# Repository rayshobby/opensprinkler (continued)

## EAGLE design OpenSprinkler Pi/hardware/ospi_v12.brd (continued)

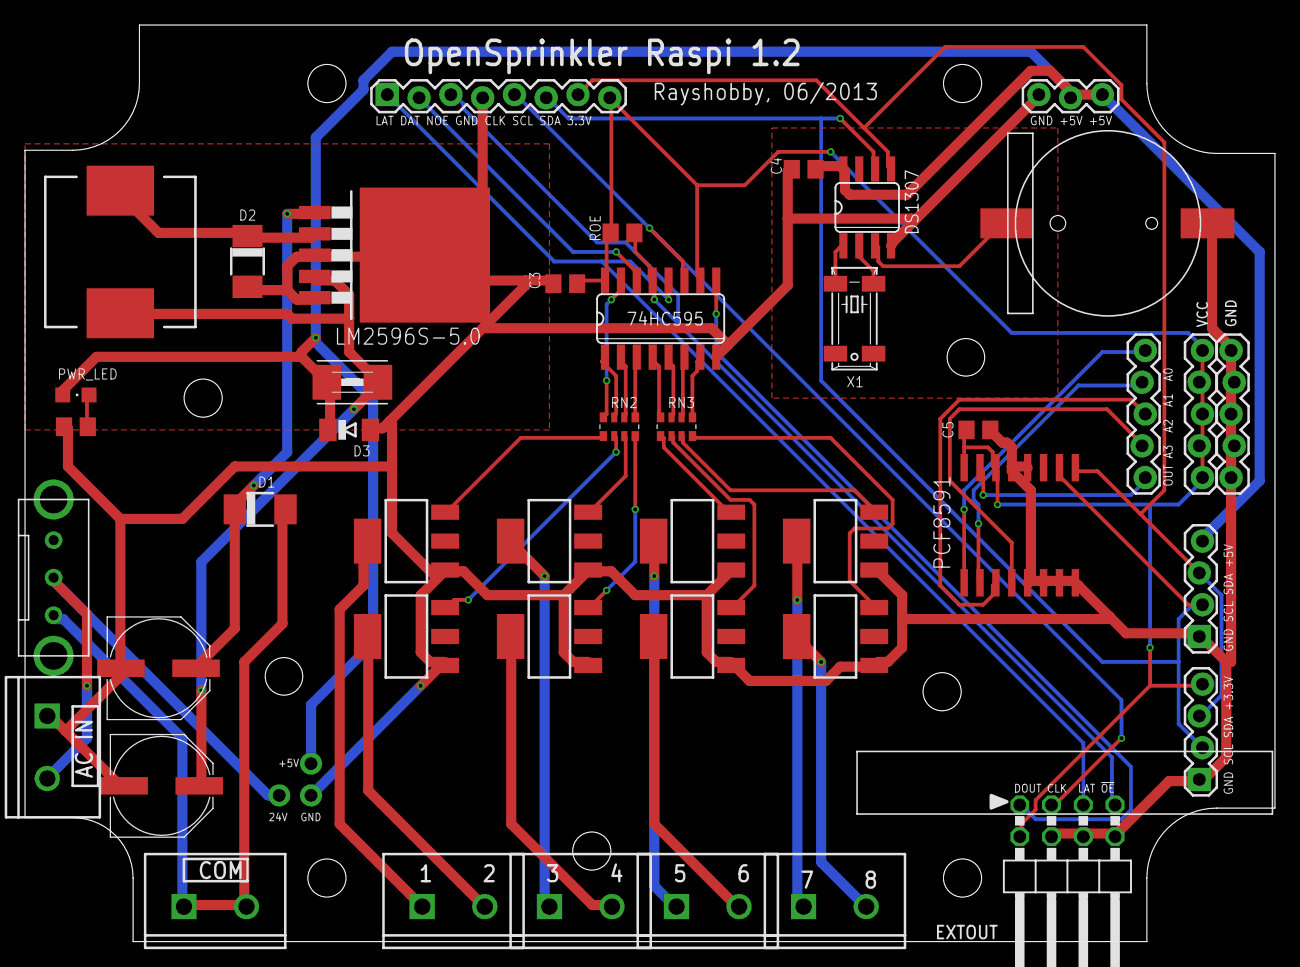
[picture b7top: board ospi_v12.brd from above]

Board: 2 copper layers, 99.9 x 73.3 mm, 48 parts (0 on the bottom side), 48 nets.

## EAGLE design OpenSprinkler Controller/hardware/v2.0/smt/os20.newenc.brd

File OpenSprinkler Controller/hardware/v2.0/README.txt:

OpenSprinkler v2.0 (2nd generation)
Changes from 1st generation:

- Microcontroller upgraded to ATmega644
- Switching regulator upgraded to LM2596S-5.0 (from MC34063)
- Added microSD card slot
- Added support for LCD backlight and contrast adjustments
- Added pull-up resistor (RPR) for automatic detection of extension boards.
- More digital and analog I/O pins, and extra pin headers for connecting RF transmitter.

Schematics and Board design files require EagleCAD v6.0 or above.

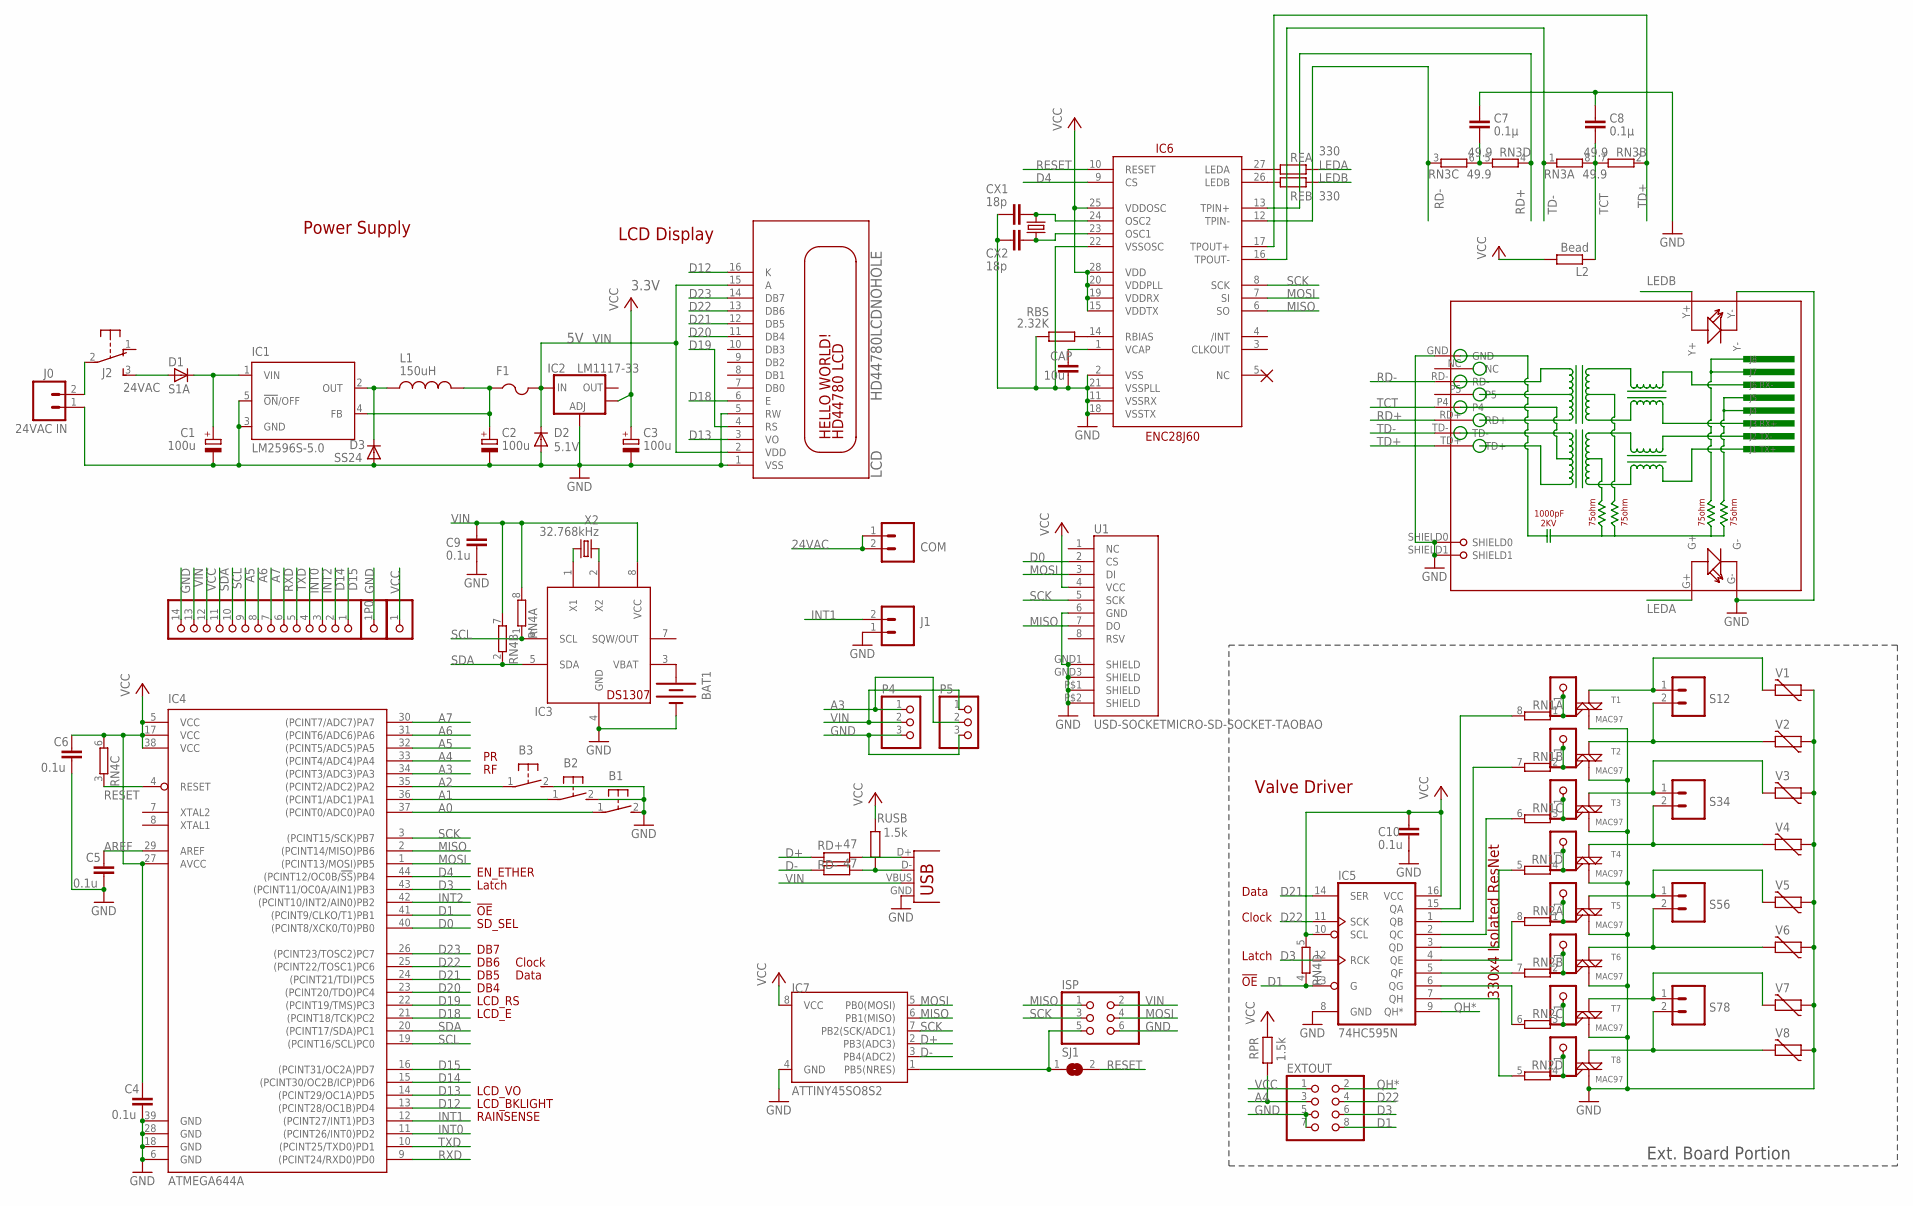
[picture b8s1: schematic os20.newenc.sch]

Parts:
B1, B2, B3: 31-XX; B3F-31XX
BAT1: BATTERYBATTERY_12MM_SMT; BATTCON_12MM_SMT
C1: 100u; E3,5-8
C2, C3: 100u; PANASONIC_D
C4, C5, C6, C9, C10: 0.1u; C0805
C7, C8: 0.1µ; C0805
CAP: 10u; C0805
COM: M025MM; SCREWTERMINAL-5MM-2
CX1, CX2: 18p; C0805
D1: S1A; DO-214AC
D2: 5.1V; MINIMELF
D3: SS24; DO-214AC
EXTOUT: PINHD-2X4; 2X04
F1: PTCFUSE-1812; 1812
IC1: LM2596S-5.0; TO263-5
IC2: LM1117-33; SOT223
IC3: DS1307; SO08
IC4: ATMEGA644A; TQFP44
IC5: 74HC595N; SO16
IC6: ENC28J60; SOIC28WLONG
IC7: ATTINY45SO8S2; SO8S2
ISP: PINHD-2X3; 2X03
J0: 24VAC IN; SCREWTERMINAL-5MM-2
J1: M025MM; SCREWTERMINAL-5MM-2
J2: EG1206
JP2, JP3, JP4, JP5, JP6, JP7, JP8, JP9: PINHD-1X1CB; 1X01-CLEANBIG
L1: 150uH; CDRH125
L2: Bead; R0805
LCD: HD44780LCDNOHOLE; LCD1602A
P0: PINHD-1X14-CB; 1X14-CB
P1, P2: PINHD-1X1CB; 1X01-CLEANBIG
P4, P5: PINHD-1X3; 1X03
RBS: 2.32K; R0805
RD+: 47; R0805
RD-: 47; R0805
REA: 330; R0805
REB: 330; R0805
RJ45: HR911105A
RN1, RN2, RN4: 4R-NEXB38V; EXB38V
RN3: 49.9; EXB38V
RPR: 1.5k; R0805
RUSB: 1.5k; R0805
S12, S34, S56, S78: M025MM; SCREWTERMINAL-5MM-2
SJ1: SJ
T1, T2, T3, T4, T5, T6, T7, T8: MAC97; SOT223
U1: USD-SOCKETMICRO-SD-SOCKET-TAOBAO; MICRO-SD-SOCKET-TAOBAO
USB: USBPTH; USB-B-PTH
V1, V2, V3, V4, V5, V6, V7, V8: MOV; R-5
X1: 25MHz; HC49US
X2: 32.768kHz; TC26H

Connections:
24VAC: COM.1, COM.2, D1.A, J2.3 (S)
A0: B1.1, IC4.37 ((PCINT0/ADC0)PA0)
A1: B2.1, IC4.36 ((PCINT1/ADC1)PA1)
A2: B3.1, IC4.35 ((PCINT2/ADC2)PA2)
A3: IC4.34 ((PCINT3/ADC3)PA3), P4.1, P5.2
A4: EXTOUT.3, IC4.33 ((PCINT4/ADC4)PA4), RPR.1
A5: IC4.32 ((PCINT5/ADC5)PA5), P0.9
A6: IC4.31 ((PCINT6/ADC6)PA6), P0.8
A7: IC4.30 ((PCINT7/ADC7)PA7), P0.7
AREF: C5.1, IC4.29 (AREF)
D0: IC4.40 ((PCINT8/XCK0/T0)PB0), U1.2 (CS)
D1: EXTOUT.8, IC4.41 ((PCINT9/CLKO/T1)PB1), IC5.13 (G), RN4.4 (1)
D3: EXTOUT.6, IC4.43 ((PCINT11/OC0A/AIN1)PB3), IC5.12 (RCK)
D4: IC4.44 ((PCINT12/OC0B/!SS!)PB4), IC6.9 (CS)
D12: IC4.13 ((PCINT28/OC1B)PD4), LCD.16 (K)
D13: IC4.14 ((PCINT29/OC1A)PD5), LCD.3 (VO)
D14: IC4.15 ((PCINT30/OC2B/ICP)PD6), P0.2
D15: IC4.16 ((PCINT31/OC2A)PD7), P0.1
D18: IC4.21 ((PCINT18/TCK)PC2), LCD.6 (E)
D19: IC4.22 ((PCINT19/TMS)PC3), LCD.4 (RS)
D20: IC4.23 ((PCINT20/TDO)PC4), LCD.11 (DB4)
D21: IC4.24 ((PCINT21/TDI)PC5), IC5.14 (SER), LCD.12 (DB5)
D22: EXTOUT.4, IC4.25 ((PCINT22/TOSC1)PC6), IC5.11 (SCK), LCD.13 (DB6)
D23: IC4.26 ((PCINT23/TOSC2)PC7), LCD.14 (DB7)
D+: IC7.2 (PB3(ADC3)), RD+.1
D-: IC7.3 (PB4(ADC2)), RD-.1
GND: B1.2 (S), B2.2 (S), B3.2 (S), BAT1.P$1 (-), C1.-, C2.-, C3.-, C4.2, C5.2, C6.2, C7.1, C8.1, C9.2, C10.2, CAP.2, CX1.2, CX2.2, D2.A, D3.A, EXTOUT.5, EXTOUT.7, IC1.3 (GND), IC1.5 (!ON!/OFF), IC2.1 (ADJ), IC3.4 (GND), IC4.6 (GND), IC4.18 (GND), IC4.28 (GND), IC4.39 (GND), IC5.8 (GND), IC6.2 (VSS), IC6.11 (VSSRX), IC6.18 (VSSTX), IC6.21 (VSSPLL), IC6.22 (VSSOSC), IC7.4 (GND), ISP.6, J0.1, J1.1, LCD.1 (VSS), LCD.5 (RW), P0.14, P1.1, P4.3, P5.3, RBS.1, RJ45.G-, RJ45.GND, RJ45.SHIELD0, RJ45.SHIELD1, RJ45.Y-, T1.1 (M1), T2.1 (M1), T3.1 (M1), T4.1 (M1), T5.1 (M1), T6.1 (M1), T7.1 (M1), T8.1 (M1), U1.6 (GND), U1.GND1 (SHIELD), U1.GND3 (SHIELD), U1.P$1 (SHIELD), U1.P$2 (SHIELD), USB.GND, V1.1, V2.1, V3.1, V4.1, V5.1, V6.1, V7.1, V8.1
INT0: IC4.11 ((PCINT26/INT0)PD2), P0.4
INT1: IC4.12 ((PCINT27/INT1)PD3), J1.2
INT2: IC4.42 ((PCINT10/INT2/AIN0)PB2), P0.3
LEDA: REA.2, RJ45.G+
LEDB: REB.2, RJ45.Y+
MISO: IC4.2 ((PCINT14/MISO)PB6), IC6.6 (SO), IC7.6 (PB1(MISO)), ISP.1, U1.7 (DO)
MOSI: IC4.1 ((PCINT13/MOSI)PB5), IC6.7 (SI), IC7.5 (PB0(MOSI)), ISP.4, U1.3 (DI)
unnamed: C1.+, D1.C, IC1.1 (VIN)
unnamed: C2.+, F1.1, IC1.4 (FB), L1.2
unnamed: JP2.1, RN1.1, T1.3 (G)
unnamed: IC5.5 (QF), RN2.7 (2)
unnamed: IC5.6 (QG), RN2.6 (2)
unnamed: J0.2, J2.2
unnamed: IC5.7 (QH), RN2.5 (2)
unnamed: IC3.1 (X1), X2.2
unnamed: D3.C, IC1.2 (OUT), L1.1
unnamed: IC5.4 (QE), RN2.8 (2)
unnamed: IC5.3 (QD), RN1.5 (2)
unnamed: IC5.2 (QC), RN1.6 (2)
unnamed: IC5.1 (QB), RN1.7 (2)
unnamed: IC5.15 (QA), RN1.8 (2)
unnamed: JP3.1, RN1.2 (1), T2.3 (G)
unnamed: S12.1, T1.4 (M2), V1.2
unnamed: S12.2, T2.4 (M2), V2.2
unnamed: S34.1, T3.4 (M2), V3.2
unnamed: JP4.1, RN1.3 (1), T3.3 (G)
unnamed: S34.2, T4.4 (M2), V4.2
unnamed: JP5.1, RN1.4 (1), T4.3 (G)
unnamed: S56.1, T5.4 (M2), V5.2
unnamed: S56.2, T6.4 (M2), V6.2
unnamed: S78.1, T7.4 (M2), V7.2
unnamed: S78.2, T8.4 (M2), V8.2
unnamed: JP6.1, RN2.1, T5.3 (G)
unnamed: JP7.1, RN2.2 (1), T6.3 (G)
unnamed: JP8.1, RN2.3 (1), T7.3 (G)
unnamed: JP9.1, RN2.4 (1), T8.3 (G)
unnamed: IC3.2 (X2), X2.1
unnamed: IC6.27 (LEDA), REA.1
unnamed: BAT1.P$2 (+), IC3.3 (VBAT)
unnamed: IC6.26 (LEDB), REB.1
unnamed: RD+.2, USB.D+
unnamed: CAP.1, IC6.1 (VCAP)
unnamed: CX1.1, IC6.24 (OSC2), X1.2
unnamed: CX2.1, IC6.23 (OSC1), X1.1
unnamed: RD-.2, RUSB.1, USB.D-
unnamed: IC7.1 (PB5(NRES)), ISP.5, SJ1.1
unnamed: C7.2, RN3.5 (2), RN3.6 (2)
unnamed: IC6.14 (RBIAS), RBS.2
QH*: EXTOUT.2, IC5.9 (QH*)
RD+: IC6.13 (TPIN+), RJ45.RD+, RN3.4 (1)
RD-: IC6.12 (TPIN-), RJ45.RD-, RN3.3 (1)
RESET: IC4.4 (RESET), IC6.10 (RESET), RN4.3 (1), SJ1.2
RXD: IC4.9 ((PCINT24/RXD0)PD0), P0.6
SCK: IC4.3 ((PCINT15/SCK)PB7), IC6.8 (SCK), IC7.7 (PB2(SCK/ADC1)), ISP.3, U1.5 (SCK)
SCL: IC3.6 (SCL), IC4.19 ((PCINT16/SCL)PC0), P0.10, RN4.1
SDA: IC3.5 (SDA), IC4.20 ((PCINT17/SDA)PC1), P0.11, RN4.2 (1)
TCT: C8.2, L2.1, RJ45.P4, RN3.7 (2), RN3.8 (2)
TD+: IC6.17 (TPOUT+), RJ45.TD+, RN3.2 (1)
TD-: IC6.16 (TPOUT-), RJ45.TD-, RN3.1
TXD: IC4.10 ((PCINT25/TXD0)PD1), P0.5
VCC: C3.+, C4.1, C6.1, C10.1, EXTOUT.1, IC2.4 (OUT), IC4.5 (VCC), IC4.17 (VCC), IC4.27 (AVCC), IC4.38 (VCC), IC5.10 (SCL), IC5.16 (VCC), IC6.15 (VDDTX), IC6.19 (VDDRX), IC6.20 (VDDPLL), IC6.25 (VDDOSC), IC6.28 (VDD), IC7.8 (VCC), L2.2, P0.12, P2.1, RN4.5 (2), RN4.6 (2), RPR.2, RUSB.2, U1.4 (VCC)
VIN: C9.1, D2.C, F1.2, IC2.3 (IN), IC3.8 (VCC), ISP.2, LCD.2 (VDD), LCD.15 (A), P0.13, P4.2, P5.1, RN4.7 (2), RN4.8 (2), USB.VBUS

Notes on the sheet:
Power Supply
Valve Driver
Data
Clock
Latch
DB4
330x4 Isolated ResNet
LCD Display
EN_ETHER
3.3V
DB7
LCD_E
LCD_RS
DB6
DB5
Ext. Board Portion
!OE
RAINSENSE
LCD_BKLIGHT
LCD_VO
SD_SEL

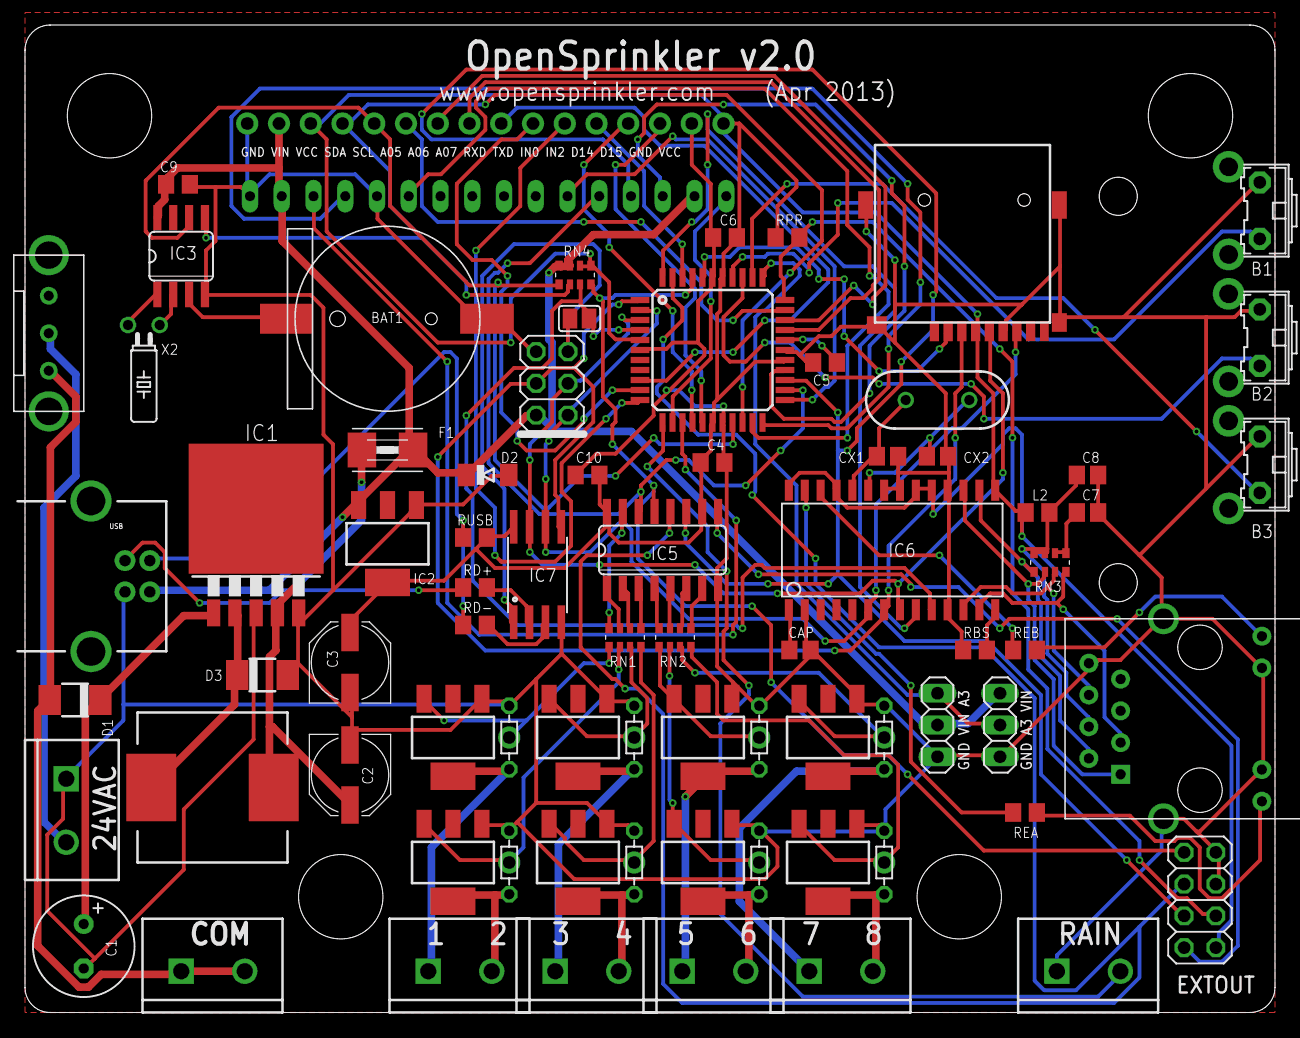
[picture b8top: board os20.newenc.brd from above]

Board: 2 copper layers, 100.0 x 79.0 mm, 87 parts (0 on the bottom side), 89 nets.

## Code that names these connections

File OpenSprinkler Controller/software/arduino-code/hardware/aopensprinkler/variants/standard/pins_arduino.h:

/*
  pins_arduino.h - Pin definition functions for Arduino
  Part of Arduino - http://www.arduino.cc/

  Copyright (c) 2007 David A. Mellis

  This library is free software; you can redistribute it and/or
  modify it under the terms of the GNU Lesser General Public
  License as published by the Free Software Foundation; either
  version 2.1 of the License, or (at your option) any later version.

  This library is distributed in the hope that it will be useful,
  but WITHOUT ANY WARRANTY; without even the implied warranty of
  MERCHANTABILITY or FITNESS FOR A PARTICULAR PURPOSE.  See the GNU
  Lesser General Public License for more details.

  You should have received a copy of the GNU Lesser General
  Public License along with this library; if not, write to the
  Free Software Foundation, Inc., 59 Temple Place, Suite 330,
  Boston, MA  02111-1307  USA

  $Id: wiring.h 249 2007-02-03 16:52:51Z mellis $

  Changelog
  -----------
  11/25/11  - ryan@ryanmsutton.com - Add pins for Sanguino 644P and 1284P
  07/15/12  - ryan@ryanmsutton.com - Updated for arduino0101
*/

#ifndef Pins_Arduino_h
#define Pins_Arduino_h

#include <avr/pgmspace.h>

#define NOT_A_PIN 0
#define NOT_A_PORT 0

#define NOT_ON_TIMER 0
#define TIMER0A 1
#define TIMER0B 2
#define TIMER1A 3
#define TIMER1B 4
#define TIMER2  5
#define TIMER2A 6
#define TIMER2B 7

#define TIMER3A 8
#define TIMER3B 9
#define TIMER3C 10
#define TIMER4A 11
#define TIMER4B 12
#define TIMER4C 13
#define TIMER5A 14
#define TIMER5B 15
#define TIMER5C 16

const static uint8_t SS   = 4;
const static uint8_t MOSI = 5;
const static uint8_t MISO = 6;
const static uint8_t SCK  = 7;

static const uint8_t SDA = 17;
static const uint8_t SCL = 16;
static const uint8_t LED_BUILTIN = 13;

static const uint8_t A0 = 31;
static const uint8_t A1 = 30;
static const uint8_t A2 = 29;
static const uint8_t A3 = 28;
static const uint8_t A4 = 27;
static const uint8_t A5 = 26;
static const uint8_t A6 = 25;
static const uint8_t A7 = 24;

// On the ATmega1280, the addresses of some of the port registers are
// greater than 255, so we can't store them in uint8_t's.
// extern const uint16_t PROGMEM port_to_mode_PGM[];
// extern const uint16_t PROGMEM port_to_input_PGM[];
// extern const uint16_t PROGMEM port_to_output_PGM[];

// extern const uint8_t PROGMEM digital_pin_to_port_PGM[];
// extern const uint8_t PROGMEM digital_pin_to_bit_PGM[];
// extern const uint8_t PROGMEM digital_pin_to_bit_mask_PGM[];
// extern const uint8_t PROGMEM digital_pin_to_timer_PGM[];

// ATMEL ATMEGA644P / SANGUINO
//
//                   +---\/---+
//  INT0 (D 0) PB0  1|        |40  PA0 (AI 0 / D31)
//  INT1 (D 1) PB1  2|        |39  PA1 (AI 1 / D30)
//  INT2 (D 2) PB2  3|        |38  PA2 (AI 2 / D29)
//   PWM (D 3) PB3  4|        |37  PA3 (AI 3 / D28)
//   PWM (D 4) PB4  5|        |36  PA4 (AI 4 / D27)
//  MOSI (D 5) PB5  6|        |35  PA5 (AI 5 / D26)
//  MISO (D 6) PB6  7|        |34  PA6 (AI 6 / D25)
//   SCK (D 7) PB7  8|        |33  PA7 (AI 7 / D24)
//             RST  9|        |32  AREF
//             VCC 10|        |31  GND 
//             GND 11|        |30  AVCC
//           XTAL2 12|        |29  PC7 (D 23)
//           XTAL1 13|        |28  PC6 (D 22)
//  RX0 (D 8)  PD0 14|        |27  PC5 (D 21) TDI
//  TX0 (D 9)  PD1 15|        |26  PC4 (D 20) TDO
//  RX1 (D 10) PD2 16|        |25  PC3 (D 19) TMS
//  TX1 (D 11) PD3 17|        |24  PC2 (D 18) TCK
//  PWM (D 12) PD4 18|        |23  PC1 (D 17) SDA
//  PWM (D 13) PD5 19|        |22  PC0 (D 16) SCL
//  PWM (D 14) PD6 20|        |21  PD7 (D 15) PWM
//                   +--------+
//
#define NUM_DIGITAL_PINS            24
#define NUM_ANALOG_INPUTS           8
#define analogInputToDigitalPin(p)  ((p < 7) ? (p) + 24 : -1)

#define digitalPinHasPWM(p)         ((p) == 3 || (p) == 4 || (p) == 12 || (p) == 13 || (p) == 14 || (p) == 15 )

#define PA 1
#define PB 2
#define PC 3
#define PD 4
#define PE 5
#define PF 6
#define PG 7
#define PH 8
#define PJ 10
#define PK 11
#define PL 12

#ifdef ARDUINO_MAIN
// these arrays map port names (e.g. port B) to the
// appropriate addresses for various functions (e.g. reading
// and writing)
const uint16_t PROGMEM port_to_mode_PGM[] =
{
        NOT_A_PORT,
        (uint16_t) &DDRA,
        (uint16_t) &DDRB,
        (uint16_t) &DDRC,
        (uint16_t) &DDRD,
};

const uint16_t PROGMEM port_to_output_PGM[] =
{
        NOT_A_PORT,
        (uint16_t) &PORTA,
        (uint16_t) &PORTB,
        (uint16_t) &PORTC,
        (uint16_t) &PORTD,
};
const uint16_t PROGMEM port_to_input_PGM[] =
{
        NOT_A_PORT,
        (uint16_t) &PINA,
        (uint16_t) &PINB,
        (uint16_t) &PINC,
        (uint16_t) &PIND,
};
const uint8_t PROGMEM digital_pin_to_port_PGM[] =
{
        PB, /* 0 */
        PB,
        PB,
        PB,
        PB,
        PB,
        PB,
        PB,
        PD, /* 8 */
        PD,
        PD,
        PD,
        PD,
        PD,
        PD,
        PD,
        PC, /* 16 */
        PC,
        PC,
        PC,
        PC,
        PC,
        PC,
        PC,
        PA, /* 24 */
        PA,
        PA,
        PA,
        PA,
        PA,
        PA,
        PA  /* 31 */
};
const uint8_t PROGMEM digital_pin_to_bit_mask_PGM[] =
{
        _BV(0), /* 0, port B */
        _BV(1),
        _BV(2),
        _BV(3),
        _BV(4),
        _BV(5),
        _BV(6),
        _BV(7),
        _BV(0), /* 8, port D */
        _BV(1),
        _BV(2),
        _BV(3),
        _BV(4),
        _BV(5),
        _BV(6),
        _BV(7),
        _BV(0), /* 16, port C */
        _BV(1),
        _BV(2),
        _BV(3),
        _BV(4),
        _BV(5),
        _BV(6),
        _BV(7),
        _BV(7), /* 24, port A */
        _BV(6),
        _BV(5),
        _BV(4),
        _BV(3),
        _BV(2),
        _BV(1),
        _BV(0)
};
const uint8_t PROGMEM digital_pin_to_timer_PGM[] =
{
        NOT_ON_TIMER,   /* 0  - PB0 */
        NOT_ON_TIMER,   /* 1  - PB1 */
        NOT_ON_TIMER,   /* 2  - PB2 */
        TIMER0A,        /* 3  - PB3 */
        TIMER0B,                /* 4  - PB4 */
        NOT_ON_TIMER,   /* 5  - PB5 */
        NOT_ON_TIMER,   /* 6  - PB6 */
        NOT_ON_TIMER,   /* 7  - PB7 */
        NOT_ON_TIMER,   /* 8  - PD0 */
        NOT_ON_TIMER,   /* 9  - PD1 */
        NOT_ON_TIMER,   /* 10 - PD2 */
        NOT_ON_TIMER,   /* 11 - PD3 */
        TIMER1B,        /* 12 - PD4 */
        TIMER1A,        /* 13 - PD5 */
        TIMER2B,        /* 14 - PD6 */
        TIMER2A,        /* 15 - PD7 */
        NOT_ON_TIMER,   /* 16 - PC0 */
        NOT_ON_TIMER,   /* 17 - PC1 */
        NOT_ON_TIMER,   /* 18 - PC2 */
        NOT_ON_TIMER,   /* 19 - PC3 */
        NOT_ON_TIMER,   /* 20 - PC4 */
        NOT_ON_TIMER,   /* 21 - PC5 */
        NOT_ON_TIMER,   /* 22 - PC6 */
        NOT_ON_TIMER,   /* 23 - PC7 */
        NOT_ON_TIMER,   /* 24 - PA0 */
        NOT_ON_TIMER,   /* 25 - PA1 */
        NOT_ON_TIMER,   /* 26 - PA2 */
        NOT_ON_TIMER,   /* 27 - PA3 */
        NOT_ON_TIMER,   /* 28 - PA4 */
        NOT_ON_TIMER,   /* 29 - PA5 */
        NOT_ON_TIMER,   /* 30 - PA6 */
        NOT_ON_TIMER   /* 31 - PA7 */
};
#endif
#endif

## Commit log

2011-12-22 version 1.2, fixed issue with changing number of slots per hour
2011-12-28 fixed missing static qualifier; added svc_simple_web program
2011-12-28 check in uncommited changes.
2011-12-28 adding optiboot bootloader to this repository.
2011-12-28 fixed a bug that causes firefox to display the webpage incorrectly.
2011-12-30 tiny change to facilitate css styling of table headers (changed a few <td> to <th>)
2012-01-21 support for 16 stations
2012-01-22 removed serial debug lines
2012-01-29 changes to support 16 stations
2012-03-21 support for potentialyl any number of ext. boards.
2012-03-21 added ntp_failure variable to detect the number of nt sync failures. the main program can use this varabile to restart the controller if the number of sync failures is more than a certain threshold.
2012-03-21 fixed opti-bootloader code size (from 31744 to 32256).
2012-03-21 added hardware update v1.1 (minor updates)
2012-03-25 added OpenSprinkler Arduino library
2012-03-25 moved svc_demo and svc_simple_web to archived folder. created new project folders.
2012-03-25 added svc_button_ctrl (replaces the previous svc_simple_web program)
2012-03-25 added back missing file.
2012-03-26 added svc_full_schedule program (replaces the previous svc_demo program
2012-03-26 temporarily remove OpenSprinkler library
2012-03-26 minor changes to svc_button_ctrl
2012-03-26 changed README file
2012-03-26 added back the OpenSprinkler library
2012-03-26 updated README files
2012-04-08 added support for master station.
2012-04-08 modified variable name
2012-04-08 misc. changes
2012-04-09 fix bug that causes the config page to not load
2012-05-12 prepare hardware update v1.2u (minor update)
2012-05-13 update component values
2012-05-17 updated OpenSprinkler library with new Wire library, added hardwre definition macro. Moved programs into the 'examples' folder
2012-05-25 Updated EtherCard files with the latest code from JeeLabs. Improved DHCP robustness
2012-05-25 move old folders to the archived directory. note that all svc programs are now in libraries->OpenSprinkler->examples folder
2012-05-26 fixed mcu type in boards.txt
2012-05-28 added compiled .hex files
2012-06-16 check in javascripts for opensprinkler
2012-06-18 deleted old scripts
2012-06-18 added new scripts
2012-06-18 added README.txt
2012-06-18 fixed bug in plotprog.js that causes infinite loop when duration is shorter than 1 minute
2012-06-18 removed old programs, added the new interval_program
2012-06-18 updated OpenSprinkler library. removed old programs, added the new interval_program
2012-06-18 archived previous firmware versions
2012-06-18 added compiled interval_program.cpp.hex
2012-06-18 fixed an issue that causes self-test to not work.
2012-06-18 updated interval_program.cpp.hex precompiled file
2012-06-18 fixed bug that causes svc_full_schedule to not accepting schedule data beyond index 256.
2012-06-20 added compiled .hex for v1.1, updated README files
2012-06-20 Update interval_program. Added manual mode.
2012-06-20 updated javascripts, added python script, added icon images
2012-06-20 minor change to home.js
2012-06-26 check in v1.3u design files, README, pin defines.
2012-06-28 check in compiled 1.3u hex file (interval program).
2012-07-07 Updated to work with Arduino 1.0 (tested on 1.0.1)
2012-07-08 Add missing include to fix Arduino 1.0 compatibility
2012-08-15 checked in hardware design v1.4 (main changes are added DS1307 RTC, and a smt variant); software update fw1.7 initial check in (main changes are two added options, support for RTC, several fixes to i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
2012-08-15 software update fw1.7 initial check in (main changes are two added options, support for RTC, several fixes to issues from the previous version, see related Readme.txt for detailed changes). Station n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
2012-08-15 check in compiled hex files
2012-08-17 increase ethernet buffer size to address the issue with preview hanging on more than 10 programs.
2012-08-17 update compiled hex files.
2012-09-14 check in firmware 1.8 javascripts
2012-09-14 check in new icons
2012-09-14 check in firmware 1.8 code
2012-09-15 modified reset handling. update compiled firmware.
2012-09-16 fix bug in ui_set_options
2012-09-16 update compiled firmware. fix button issue in setup options
2012-09-17 added custom lcd character for network status. compacted self-test function to make space
2012-09-17 updated compiled firmware
2012-09-17 comment out SVC_HW_VERSION
2012-09-24 remove support for concurrent running mode (due to a temporarily unsolvable buy). fix a bug that skips program checking when the water duration is in multiples of 60 minutes.
2012-09-27 change RTC sync interval to 15 minutes. commit new compiled firmware.
2012-09-28 change RTC interval to 1 minute, add firmware minor version number, more accurate per-second level water time.
2012-10-30 fixes to buffer overflow on 32 stations; new javascript features; David Gustavson's PHP logging scripts; firmware version is changed to 1.8.2
2012-11-05 update David's logging scripts
2013-01-01 check in Dan's raspi scripts
2013-01-27 fix javascript that causes preview to sometime show the wrong date
2013-02-03 further fix of Javascript for program preview feature
2013-02-03 check in compiled firmware 1.7, the latest that supports concurrent running mode
2013-02-10 check in firmware 1.8.3. main chnages are 1) added back support for concurrent running mode; 2) new 'device_id' option which allows modifying the last byte of the controller's mac address.
2013-02-18 check in OSPi hardware design and software demos
2013-02-18 check in OSPi documents
2013-02-18 change diagram file name
2013-03-09 fix component values
2013-03-14 add fix to GPIO defines for RPi rev.2
2013-03-22 Create openheat
2013-04-10 check in v1.42u hardware design files
2013-04-28 check in OpenSprinkler 2.0 (SMT version) hardware design files
2013-04-28 Change folder names; check in precompiled firmware v2.0.0
2013-04-30 check in vusbtiny source code
2013-05-25 check in interval_program for OSPi written by Dan
2013-05-25 minor changes to README.txt
2013-05-28 updated readme with correct settings for auto start of the interval_program.
    ## If you aren't sure that the path to python on your Pi is /usr/bin/, use whereis python to determine the location
    /usr/bin/python ospi.py $host$port
2013-06-09 add OSPi v1.1 Eagle files
2013-06-09 add OSPi hardware README.txt
2013-06-16 updated scripts from Dan. removed the unzipped folder
2013-06-18 check in OpenSprinkler 2.0 Arduino code
2013-06-18 change folder name
2013-06-18 add link to instructions for compiling source code
2013-06-19 apply Samer's patch to OSPi interval program
2013-06-23 check in Dan's code (Jun 22, 2013 update)
2013-06-23 change back the ospi file name
2013-06-26 Bug fixes Jun 26 2013
2013-06-27 update Jun 26, 2013
2013-07-07 check in Jun 26 update of Dan's OSPi interval_program
2013-07-07 add back the source folder for OSPi interval_program
2013-07-08 check in OSPi v1.2 hardware design files and update README.txt
2013-07-11 check in Dan's OSPi interval_program Jul 10 update
2013-07-20 check in Dan's OSPi interval_program July 19 update
2013-07-21 check in Dan's interval_program July 21 update
2013-08-03 check in Dan's OSPi interval_program Aug 1 update (firmware 1.8.3)
2013-08-27 Generalized options handling
    1. New format for options.txt that consolidates editing metadata
    (label, name, datatype, tooltip), removes runtime data
    2. Generalized passing of options into Javascript, as an "sd" object.
    Helper function for populating this object in ospi.py
    3. Converted "loc" into a standard, editable option, added
    "station_name_length" option (non-editable).
2013-10-17 check in firmware 2.0.1 compiled version with instructions
2013-10-17 Moved current OSPi program to archive folder. The most recent version of OSPi's interval program is now hosted at Dan's Github page, and no longer maintained at Rayshobby Github page.
2013-10-17 check in firmware 2.0.1 source code
2013-11-11 check in firmware 2.0.2, added JSON support; controller operation bit, manual mode, and rain delay time are stored in EEPROM
2013-12-30 Check in compiled firmware 2.0.3 and updated README files
2014-01-05 check in firmware 2.0.3 source code
2014-02-11 update Arduino delay function to incorporate 12MHz clock speed
2014-02-24 check in hardware v2.1 hardware design files
2014-02-24 check in firmware 2.0.4. this firmware goes with the new mobile app. also added lcd auto-dimming.
2014-02-26 remove old compiled folder. Check in new osFimrwareUpdater folder. osFirmwareUpdater is a GUI-based firmware updater tool.
2014-02-26 remove old README.txt from compiled folder
2014-02-26 check in compiled firmware 2.0.4
2014-02-26 fix bug in os_firmware_info.txt
2014-04-06 check in OSPi v1.3 hardware design files
2014-05-07 check in firmware 2.0.5. added support for per-station ignore-rain bit
2014-06-09 check in expansion board 2.0 hardware files
2014-06-13 check in firmware 2.0.6 code and pre-compiled hex file
2014-07-05 check in firmware 2.0.7
2014-07-23 check in fw2.0.7 source code
2014-08-25 check in firmware 2.0.8
2014-08-25 Check in firmware 2.0.8 source code. This firmware adds support for relay, logging rain sensor / rain delay status. The default UI has been changed to Samer's mobile UI
2014-09-04 check in firmware 2.0.9. fixed issue in 2.0.8 where SPACE characeter is not allowed in station name / location. also refined cache directives in HTTP headers.
2014-09-04 remove old copy_to_sd card folder
2014-09-04 Update osFirmwareUpdater.pde
    Added button to get the latest firmware files.
2014-09-10 check in new osFirmwareUpdater program
2014-09-24 check in compiled firmware 2.1.0
2014-09-24 fix bug in firmware2.1.0beta that generates wrong log records when turning off a station that's not running
2014-09-26 add OpenSprinkler 2.2 compiled firmwares
2014-09-26 check in new Qt-based firmware updater source code. Remove Processing-based one
2014-10-22 check in firmware 2.1.0 Arduino code. for intermediate changes, please check the development thread at https://github.com/OpenSprinkler/OpenSprinklerGen2
2014-10-22 Update readme.txt to add note for fw2.1.0. Update notes for old firmware updater program
2014-10-26 add weather code
2014-10-26 add OSPi 1.4 and 1.4 B+ hardware design files
2014-10-27 add OpenSprinkler 2.2 board profile
2014-10-28 add OSDIY 2.2 hardware files and update notes
2014-12-03 check in firmware 2.1.1 source code. update release notes
2014-12-05 add hardware design files for OS 2.2 DIY Nov 14 revision, and OS 2.2s
2014-12-16 check in firmware 2.1.2 source code
2015-01-22 change atmega644 to atmega644p
2015-02-04 - added google calendar demo option to select_program
2015-02-04 made significant changes to stock google calendar demo, including - add support for google api v3 - pull common config items from environment variables (can be set in /etc/default/ospi_gc if running 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
2015-03-18 add OpenSprinkler 2.3 profile to Arduino boards.txt
2015-08-03 add OS 2.3 AC and DC hardware design files
2015-08-03 correct some component values
2015-08-03 commited the wrong png files
2015-08-12 check in v1.42+ EagleCAD files
2016-11-06 move older versions to archive folder
2016-11-06 again, move older versions to archive folder
2016-11-06 add new version ospi_v143+, with laser cut enclosure design
2016-11-06 add enclosure design .ai file, modify README.txt
